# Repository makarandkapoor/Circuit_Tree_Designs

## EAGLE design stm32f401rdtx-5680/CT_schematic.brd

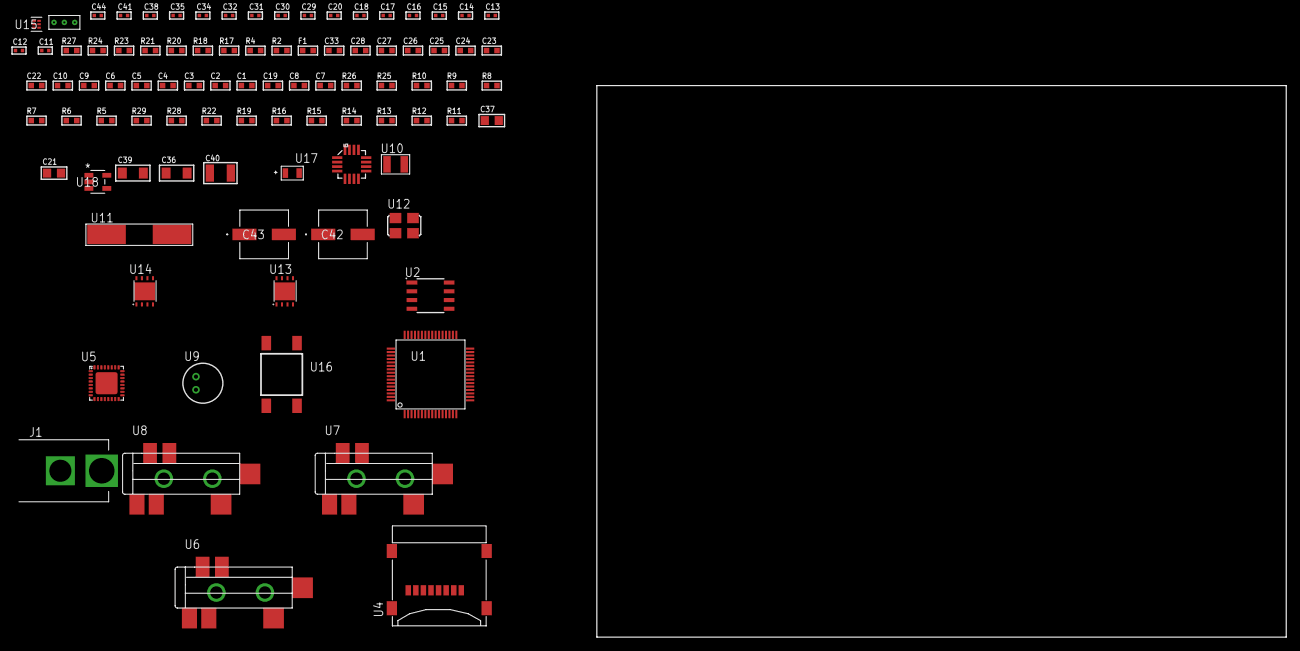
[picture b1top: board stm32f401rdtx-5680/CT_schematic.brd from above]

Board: 2 copper layers, 100.0 x 80.0 mm, 92 parts (0 on the bottom side), 60 nets, no tracks yet.

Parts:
C1, C10, C22, C23, C24, C25, C26, C27, C28, C33: 1e-06; C0603
C2, C3, C4, C5, C6: 1e-07; C0603
C7: 4.7e-06; C0603
C8: 2.2e-06; C0603
C9: 1e-08; C0603
C11, C12, C13, C14: 1e-11; C0402
C15, C16, C17, C18, C34, C35, C38, C44: 1e-08; C0402
C19: 4.7e-07; C0603
C20, C29, C30, C31, C32, C41: 1e-07; C0402
C21, C37: 1e-05; C0805
C36, C39: 1e-05; C1206
C40: 1e-05; C1210
C42, C43: 0.0001; EXV-9H
F1: 240.0; L0603
J1: PJ-037B; PJ-037B_PACKAGE
R2, R21, R24: 1000.0; R0603
R4: 4700.0; R0603
R5, R6, R7, R8, R9, R10, R25, R26: 10000.0; R0603
R11, R12, R13, R14, R15, R16, R19, R22: 100000.0; R0603
R17, R18: 1270.0; R0603
R20: 200.0; R0603
R23: 2231.0; R0603
R27: 9100.0; R0603
R28: 680000.0; R0603
R29: 120000.0; R0603
U1: STM32F401RDT6; LQFP64
U2: AT25320B-SSHL-T; SOIC-8
U3: l3g4200d; LGA-16
U4: 0472192001; MOLEX_47219-2001
U5: SGTL5000XNAA3; QFN-32
U6, U7, U8: SJ-43515TS-SMT-TR
U9: WM-64PCT; WM-64PC
U10: ABS07-32.768KHZ-7-T
U11: ABLS-25.000MHZ-B2F-T
U12: ASFL-24.57MHZ-NCS; ASFL1
U13, U14: LP3878SDX-ADJ/NOPB; WSON-8
U15: TPS3895ADRYR; SON-6
U16: 4-1437565-2; SW_4-1437565-2
U17: Q65110A2395; LGM67K-G1J2-24-Z
U18: nc7sz125m5x; NC7SZ125M5X
U19: Dummy; DUMMY_PACKAGE_195

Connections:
CLK_CRYSTAL_U1_3: C11.1, U1.3, U10.1
CLK_CRYSTAL_U1_4: C12.1, U1.4, U10.2
CLK_CRYSTAL_U1_5: C13.1, U1.5, U11.1
CLK_CRYSTAL_U1_6: C14.1, U1.6, U11.2
CLK_U5_21: U5.21, U12.3
GND: C1.2, C2.2, C3.2, C4.2, C5.2, C6.2, C7.2, C8.2, C9.2, C10.2, C11.2, C12.2, C13.2, C14.2, C15.2, C16.2, C17.2, C18.2, C20.2, C21.2, C29.2, C30.2, C31.2, C32.2, C33.2, C34.2, C35.2, C36.2, C37.2, C38.2, C39.2, C40.2, C41.2, C42.2, C43.2, C44.2, J1.2, R2.2, R5.2, R9.1, R9.2, R18.2, R21.2, R24.2, R27.2, R29.2, U1.12, U1.18, U1.31, U1.47, U1.63, U2.4, U3.8, U3.9, U3.10, U3.11, U3.12, U3.13, U4.6, U4.G1, U4.G2, U4.G3, U4.G4, U5.1, U5.3, U5.7, U5.EXP, U7.1, U8.1, U9.2, U12.2, U13.3, U13.PAD, U14.3, U14.PAD, U15.2, U17.C, U18.1, U18.3, U19.1
NET_U1_7: R4.1, U1.7, U18.4
NET_U1_13: C9.1, C10.1, F1.1, U1.13
NET_U1_30: C8.1, U1.30
NET_U1_60: R5.1, U1.60
NET_U1_61: U16.3, U16.4
NET_U2_3: R6.1, U2.3
NET_U2_7: R8.1, U2.7
NET_U3_14: C18.1, C19.1, U3.14
NET_U5_10: C32.1, U5.10
NET_U5_29: R17.1, U5.29
NET_U5_31: R18.1, U5.31
NET_U6_1: U5.4, U6.1
NET_U6_2: U5.2, U6.2
NET_U6_5: U5.6, U6.5
NET_U7_2: C23.1, U7.2
NET_U7_5: C22.1, U7.5
NET_U8_2: C25.1, C26.1, U8.2
NET_U8_5: C24.1, U8.5
NET_U8_13: C25.2, C26.2
NET_U9_1: C27.1, C28.1, C33.1, U5.16, U9.1
NET_U9_15: C27.2, C28.2
NET_U13_1: C35.1, U13.1
NET_U13_6: R20.2, R21.1, U13.6
NET_U13_8: R19.1, U13.8
NET_U14_1: C38.1, U14.1
NET_U14_6: R23.2, R24.1, U14.6
NET_U14_8: R22.1, U14.8
NET_U15_1: R26.1, R27.1, U15.1
NET_U15_3: R28.2, R29.1, U15.3
NET_U15_4: R25.1, U15.4, U18.2
NET_U16_1: R2.1, U16.1, U16.2
PROC_ADC1_IN1: U1.15, U19.3
PROC_ADC1_IN2: U1.16, U19.2
PROC_I2S2_CK: U1.34, U5.24
PROC_I2S2_EXT_SD: U1.35, U5.25
PROC_I2S2_SD: U1.36, U5.26
PROC_I2S2_WS: U1.62, U5.23
PROC_SDIO_CK: R12.1, U1.53, U4.5
PROC_SDIO_CMD: R11.1, U1.54, U4.3
PROC_SDIO_D0: R13.1, U1.39, U4.7
PROC_SDIO_D1: R14.1, U1.40, U4.8
PROC_SDIO_D2: R15.1, U1.51, U4.1
PROC_SDIO_D3: R16.1, U1.52, U4.2
PROC_SPI1_MISO: U1.22, U3.4
PROC_SPI1_MOSI: U1.23, U3.3
PROC_SPI1_NSS: R10.1, U1.20, U3.5
PROC_SPI1_SCK: U1.21, U3.2
PROC_SPI2_MISO: U1.10, U2.2
PROC_SPI2_MOSI: U1.11, U2.5
PROC_SPI2_NSS: R7.1, U1.33, U2.1
PROC_SPI2_SCK: U1.29, U2.6
VCC_S1_9V6: C36.1, C39.1, C42.1, C43.1, J1.1, R19.2, R22.2, U13.4, U14.4
VCC_TIER1_1V2: C29.1, C37.1, R20.1, U5.30, U13.5
VCC_TIER1_3V3: C1.1, C2.1, C3.1, C4.1, C5.1, C6.1, C7.1, C15.1, C16.1, C17.1, C20.1, C21.1, C30.1, C31.1, C34.1, C40.1, C41.1, C44.1, F1.2, R4.2, R6.2, R7.2, R8.2, R10.2, R11.2, R12.2, R13.2, R14.2, R15.2, R16.2, R17.2, R23.1, R25.2, R26.2, R28.1, U1.1, U1.19, U1.32, U1.48, U1.64, U2.8, U3.1, U3.15, U3.16, U4.4, U5.5, U5.20, U12.4, U14.5, U15.6, U18.5

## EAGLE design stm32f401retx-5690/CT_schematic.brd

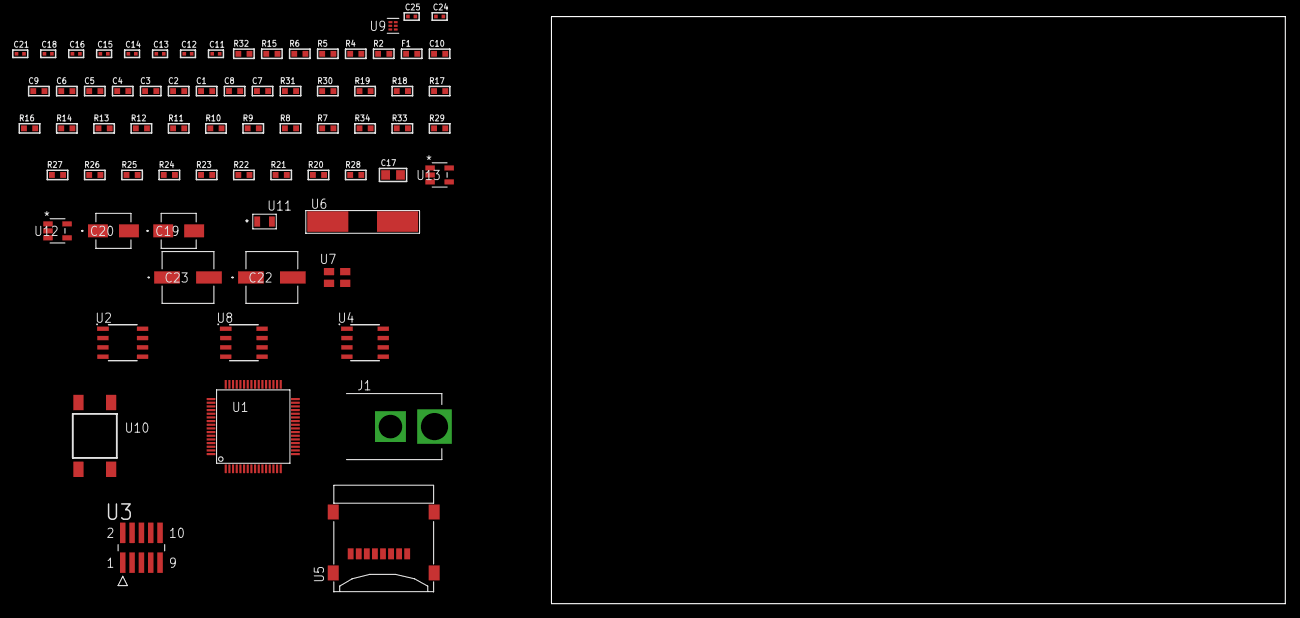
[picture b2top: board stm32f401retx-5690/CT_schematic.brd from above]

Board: 2 copper layers, 100.0 x 80.0 mm, 72 parts (0 on the bottom side), 42 nets, no tracks yet.

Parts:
C1, C10: 1e-06; C0603
C2, C3, C4, C5, C6: 1e-07; C0603
C7: 4.7e-06; C0603
C8: 2.2e-06; C0603
C9: 1e-08; C0603
C11, C12: 1e-11; C0402
C13, C15, C18, C24, C25: 1e-08; C0402
C14, C16, C21: 1e-07; C0402
C17: 1e-05; C0805
C19: 1e-06; EXV-9B
C20: 2.2e-06; EXV-9B
C22, C23: 0.0001; EXV-9H
F1: 240.0; L0603
J1: PJ-037B; PJ-037B_PACKAGE
R2: 1000.0; R0603
R4: 4700.0; R0603
R5, R6: 2200.0; R0603
R7, R8, R9, R10, R11, R12, R13, R14, R16, R17, R18, R19, R30, R31: 10000.0; R0603
R15: 5.0; R0603
R20, R21, R22, R23, R24, R25, R26, R27, R29: 100000.0; R0603
R28: 164658.62; R0603
R32: 9100.0; R0603
R33: 680000.0; R0603
R34: 120000.0; R0603
U1: STM32F401RET6; LQFP64
U2: AT25040B-SSHL-T; SOIC-8
U3: FTSH-105-01-L-DV-K; SAMTEC_FTSH-105-01-L-DV-K
U4: AT24C02D-SSHM-T; AT24C02D
U5: 0472192001; MOLEX_47219-2001
U6: ABLS-25.000MHZ-B2F-T
U7: ASEK-32.768KHz-ECST; ASEK
U8: LP2954AIMX/NOPB; LP2954
U9: TPS3895ADRYR; SON-6
U10: 4-1437565-2; SW_4-1437565-2
U11: Q65110A2395; LGM67K-G1J2-24-Z
U12, U13: nc7sz125m5x; NC7SZ125M5X

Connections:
CLK_CRYSTAL_U1_5: C11.1, U1.5, U6.1
CLK_CRYSTAL_U1_6: C12.1, U1.6, U6.2
CLK_U1_3: U1.3, U7.3
GND: C1.2, C2.2, C3.2, C4.2, C5.2, C6.2, C7.2, C8.2, C9.2, C10.2, C11.2, C12.2, C13.2, C14.2, C15.2, C16.2, C17.2, C18.2, C19.2, C20.2, C21.2, C22.2, C23.2, C24.2, C25.2, J1.2, R2.2, R7.2, R14.2, R15.2, R16.2, R18.2, R19.2, R29.2, R32.2, R34.2, U1.12, U1.18, U1.31, U1.47, U1.63, U2.4, U3.3, U3.5, U4.4, U5.6, U5.G1, U5.G2, U5.G3, U5.G4, U7.2, U8.4, U9.2, U11.C, U12.2, U12.3, U13.1, U13.3
NET_U1_7: R4.1, U1.7, U13.4
NET_U1_13: C9.1, C10.1, F1.1, U1.13
NET_U1_30: C8.1, U1.30
NET_U1_58: R5.1, U1.58, U4.6
NET_U1_59: R6.1, U1.59, U4.5
NET_U1_60: R7.1, U1.60
NET_U1_62: U10.3, U10.4
NET_U2_3: R8.1, U2.3
NET_U2_7: R10.1, U2.7
NET_U3_9: R15.1, U3.9
NET_U4_1: R17.1, U4.1
NET_U4_2: R18.1, U4.2
NET_U4_3: R19.1, U4.3
NET_U4_7: R16.1, U4.7
NET_U8_3: R27.1, U8.3
NET_U8_5: R26.1, U8.5
NET_U8_7: R28.2, R29.1, U8.7
NET_U9_1: R31.1, R32.1, U9.1
NET_U9_3: R33.2, R34.1, U9.3
NET_U9_4: R30.1, U9.4, U12.4, U13.2
NET_U10_1: R2.1, U10.1, U10.2
PROC_SDIO_CK: R21.1, U1.53, U5.5
PROC_SDIO_CMD: R20.1, U1.54, U5.3
PROC_SDIO_D0: R22.1, U1.39, U5.7
PROC_SDIO_D1: R23.1, U1.40, U5.8
PROC_SDIO_D2: R24.1, U1.51, U5.1
PROC_SDIO_D3: R25.1, U1.52, U5.2
PROC_SPI1_MISO: U1.22, U2.2
PROC_SPI1_MOSI: U1.23, U2.5
PROC_SPI1_NSS: R9.1, U1.20, U2.1
PROC_SPI1_SCK: U1.21, U2.6
PROC_SYS_JTCK_SWCLK: R14.1, U1.49, U3.4
PROC_SYS_JTDI: R12.1, U1.50, U3.8
PROC_SYS_JTDO_SWO: U1.55, U3.6
PROC_SYS_JTMS_SWDIO: R13.1, U1.46, U3.2
RST_OUT_U3_JTAG_RST_B: R11.1, U3.10, U12.1
VCC_S1_10V3: C19.1, C22.1, C23.1, J1.1, R27.2, U8.8
VCC_TIER1_3V3: C1.1, C2.1, C3.1, C4.1, C5.1, C6.1, C7.1, C13.1, C14.1, C15.1, C16.1, C17.1, C18.1, C20.1, C21.1, C24.1, C25.1, F1.2, R4.2, R5.2, R6.2, R8.2, R9.2, R10.2, R11.2, R12.2, R13.2, R17.2, R20.2, R21.2, R22.2, R23.2, R24.2, R25.2, R26.2, R28.1, R30.2, R31.2, R33.1, U1.1, U1.19, U1.32, U1.48, U1.64, U2.8, U3.1, U4.8, U5.4, U7.4, U8.1, U9.6, U12.5, U13.5

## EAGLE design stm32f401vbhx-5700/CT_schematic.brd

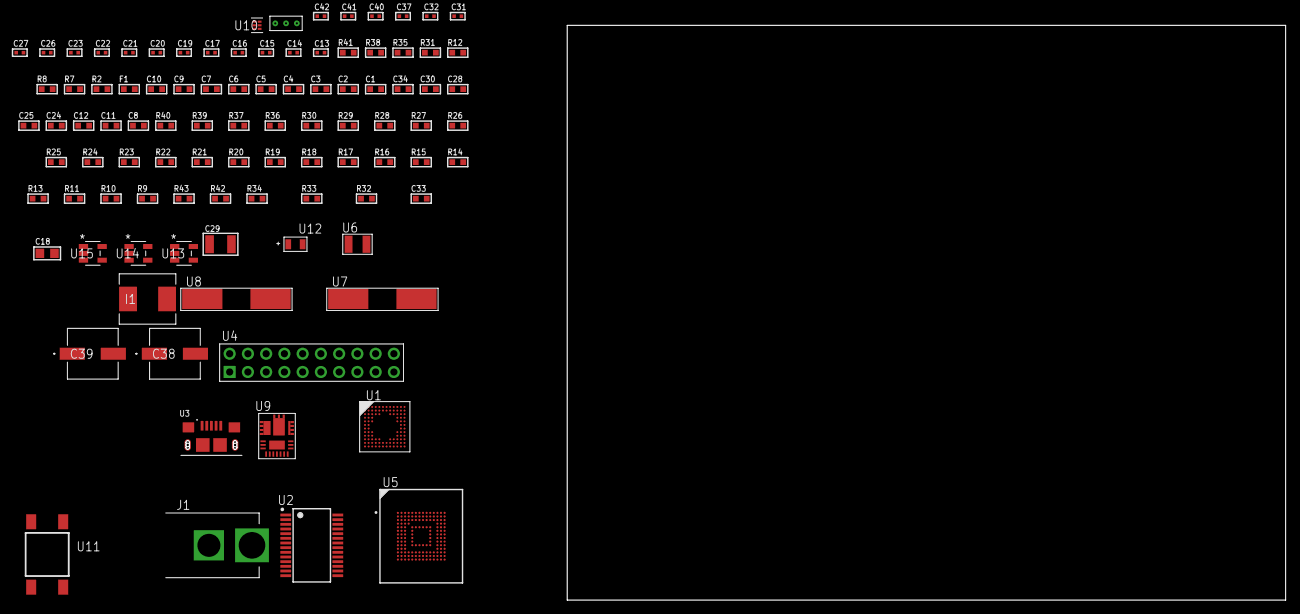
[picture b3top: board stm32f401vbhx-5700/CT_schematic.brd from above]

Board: 2 copper layers, 97 parts (0 on the bottom side), 62 nets, no tracks yet.

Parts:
C1, C10: 1e-06; C0603
C2, C3, C4, C5, C6, C7: 1e-07; C0603
C8: 4.7e-06; C0603
C9: 1e-08; C0603
C11, C12, C24, C25, C28, C30: 2.2e-06; C0603
C13, C14, C15, C16: 1e-11; C0402
C17, C19, C20, C21, C22, C23, C26, C27, C31, C32, C37: 1e-07; C0402
C18: 4.7e-06; C0805
C29: 0.0001; C1210
C33: 7.8444498006919e-09; R0603
C34: 2.7e-07; C0603
C38, C39: 0.0001; EXV-9H
C40, C41, C42: 1e-08; C0402
F1: 240.0; L0603
I1: 6.8e-07; IND25X25CZ
J1: PJ-037B; PJ-037B_PACKAGE
R2: 1000.0; R0603
R7, R8, R12: 4700.0; R0603
R9, R10, R11, R13, R14, R15, R16, R17, R18, R19, R20, R39, R40: 10000.0; R0603
R21, R22, R23, R24, R25, R26, R27, R28, R29, R30: 34000.0; R0603
R31: 0.1; R0603
R32: 4030.2416170974; R0603
R33: 719.68600305311; R0603
R34: 64.984347826087; R0603
R35: 130.0; R0603
R36: 39000.0; R0603
R37: 49900.0; R0603
R38: 5600.0; R0603
R41: 9100.0; R0603
R42: 680000.0; R0603
R43: 120000.0; R0603
U1: STM32F401VBH6; UFBGA100
U2: FT232RL-REEL; SSOP-28
U3: 10118193-0001LF; FCI_10118193-0001LF
U4: TST-110-05-T-D-RA
U5: mtfc4gmcdm; TFBGA-153
U6: ABS07-32.768KHZ-7-T
U7: ABLS-25.000MHZ-B2F-T
U8: ABLS-12.000MHZ-B4-T
U9: IR3899MTR1PBF
U10: TPS3895ADRYR; SON-6
U11: 4-1437565-2; SW_4-1437565-2
U12: Q65110A2395; LGM67K-G1J2-24-Z
U13, U14, U15: nc7sz125m5x; NC7SZ125M5X
U16: Dummy; DUMMY_PACKAGE_207

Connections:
CLK_CRYSTAL_U1_D1: C13.1, U1.D1, U6.1
CLK_CRYSTAL_U1_E1: C14.1, U1.E1, U6.2
CLK_CRYSTAL_U1_F1: C15.1, U1.F1, U7.1
CLK_CRYSTAL_U1_G1: C16.1, U1.G1, U7.2
CLK_CRYSTAL_U2_27: U2.27, U8.1
CLK_CRYSTAL_U2_28: U2.28, U8.2
GND: C1.2, C2.2, C3.2, C4.2, C5.2, C6.2, C7.2, C8.2, C9.2, C10.2, C11.2, C12.2, C13.2, C14.2, C15.2, C16.2, C17.2, C18.2, C19.2, C20.2, C21.2, C22.2, C23.2, C24.2, C25.2, C26.2, C27.2, C28.2, C30.2, C31.2, C32.2, C37.2, C38.2, C39.2, C40.2, C41.2, C42.2, J1.2, R2.2, R9.2, R11.2, R14.2, R20.2, R31.1, R31.2, R33.2, R36.2, R38.2, R41.2, R43.2, U1.D3, U1.F2, U1.F11, U1.F12, U1.J1, U1.K1, U2.7, U2.18, U2.21, U2.25, U2.26, U3.5, U3.6, U3.7, U3.8, U3.9, U4.4, U4.6, U4.8, U4.10, U4.12, U4.14, U4.16, U4.18, U4.20, U5.C4, U5.E7, U5.G5, U5.H10, U5.K8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
NET_U1_A4: R9.1, U1.A4
NET_U1_C11: C12.1, U1.C11
NET_U1_E3: R11.1, U1.E3
NET_U1_H2: R8.1, U1.H2, U15.4
NET_U1_H3: R10.1, U1.H3
NET_U1_L11: C11.1, U1.L11
NET_U1_M1: C9.1, C10.1, F1.1, U1.L1, U1.M1
NET_U1_M12: U11.3, U11.4
NET_U2_14: R13.1, U2.14
NET_U2_17: C19.1, U2.17
NET_U2_19: R14.1, U2.19
NET_U3_1: R12.1, U3.1
NET_U3_2: U2.16, U3.2
NET_U3_3: U2.15, U3.3
NET_U4_19: R20.1, U4.19
NET_U5_C2: C25.1, C26.1, U5.C2
NET_U5_K5: R7.1, U5.K5, U14.4
NET_U9_1: C33.1, R32.1, R33.1, R34.1, R35.1, U9.1, U9.8
NET_U9_2: C32.1, U9.2
NET_U9_3: C33.2, C34.1, C34.2, U9.3
NET_U9_5: R36.1, U9.5
NET_U9_10: C30.1, U9.10
NET_U9_12: C29.1, I1.1, U9.12
NET_U9_14: C29.2, U9.14
NET_U9_15: R37.1, R38.1, U9.15
NET_U9_ATNET_3: I1.2, R32.2
NET_U9_ATNET_4: C34.2, R34.2
NET_U10_1: R40.1, R41.1, U10.1
NET_U10_3: R42.2, R43.1, U10.3
NET_U10_4: R39.1, U10.4, U13.4, U14.2, U15.2
NET_U11_1: R2.1, U11.1, U11.2
PROC_ADC1_IN1: U1.M2, U16.3
PROC_ADC1_IN2: U1.K3, U16.2
PROC_SDIO_CK: R30.1, U1.B10, U5.M6
PROC_SDIO_CMD: R29.1, U1.C8, U5.M5
PROC_SDIO_D0: R21.1, U1.E10, U5.A3
PROC_SDIO_D1: R22.1, U1.D12, U5.A4
PROC_SDIO_D2: R23.1, U1.B11, U5.A5
PROC_SDIO_D3: R24.1, U1.C10, U5.B2
PROC_SDIO_D4: R25.1, U1.A3, U5.B3
PROC_SDIO_D5: R26.1, U1.B3, U5.B4
PROC_SDIO_D6: R27.1, U1.E12, U5.B5
PROC_SDIO_D7: R28.1, U1.E11, U5.B6
PROC_SYS_JTCK_SWCLK: R18.1, U1.A10, U4.9
PROC_SYS_JTDI: R16.1, U1.A9, U4.5
PROC_SYS_JTDO_SWO: U1.A8, U4.13
PROC_SYS_JTMS_SWDIO: R17.1, U1.A11, U4.7
PROC_SYS_JTRST: R15.1, U1.A7, U4.3
PROC_USART1_CTS: U1.B12, U2.3
PROC_USART1_RTS: U1.A12, U2.11
PROC_USART1_RX: U1.B4, U2.1
PROC_USART1_TX: U1.B5, U2.5
RST_OUT_U4_SRESET_B: R19.1, U4.15, U13.1
VCC_S1_16V1: C31.1, C38.1, C39.1, J1.1, R37.2, U9.9
VCC_TIER1_3V3: C1.1, C2.1, C3.1, C4.1, C5.1, C6.1, C7.1, C8.1, C17.1, C18.1, C20.1, C21.1, C22.1, C23.1, C24.1, C27.1, C28.1, C37.1, C40.1, C41.1, C42.1, F1.2, I1.2, R7.2, R8.2, R10.2, R13.2, R15.2, R16.2, R17.2, R18.2, R19.2, R21.2, R22.2, R23.2, R24.2, R25.2, R26.2, R27.2, R28.2, R29.2, R30.2, R32.2, R39.2, R40.2, R42.1, U1.C4, U1.E2, U1.G2, U1.G11, U1.G12, U2.4, U2.20, U4.1, U4.2, U5.C6, U5.E6, U5.F5, U5.J10, U5.K9, U5.M4, U5.N4, U5.P3, U5.P5, U10.6, U13.5, U14.5, U15.5

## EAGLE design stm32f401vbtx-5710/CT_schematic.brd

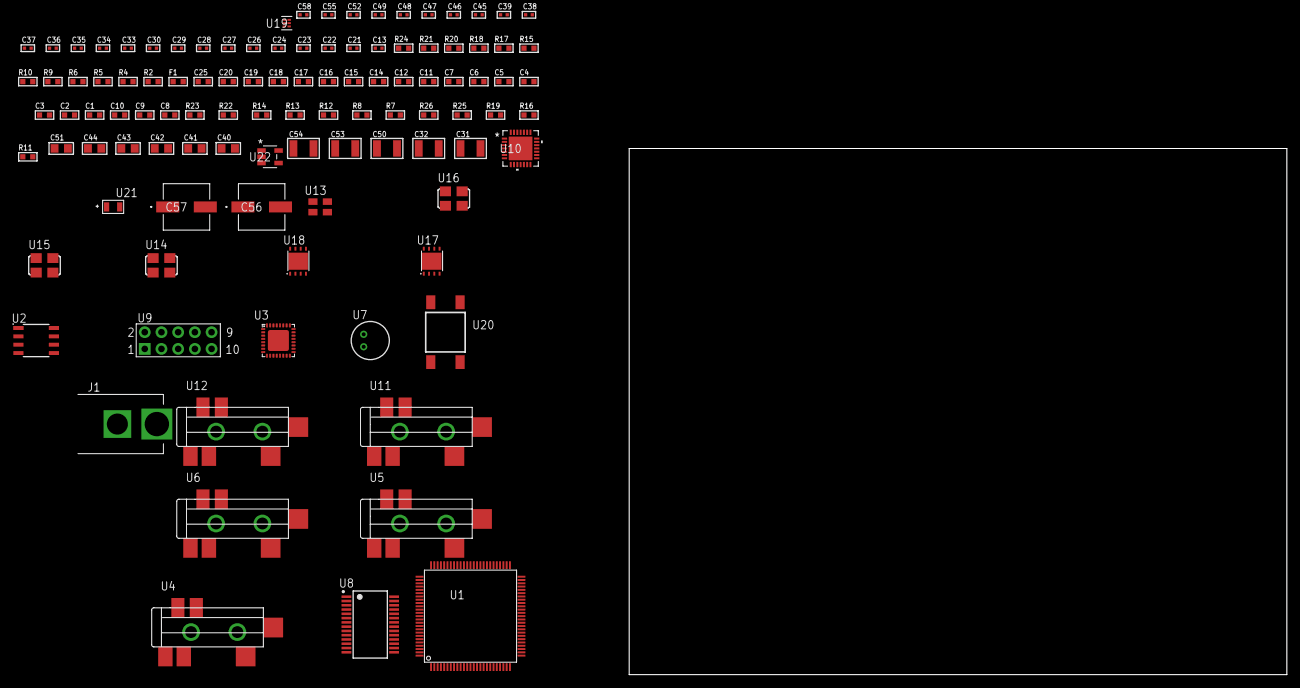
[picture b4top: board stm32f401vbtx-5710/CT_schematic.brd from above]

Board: 2 copper layers, 100.0 x 80.0 mm, 106 parts (0 on the bottom side), 67 nets, no tracks yet.

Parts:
C1, C12, C14, C15, C16, C17, C18, C19, C20, C25: 1e-06; C0603
C2, C3, C4, C5, C6, C7: 1e-07; C0603
C8: 4.7e-06; C0603
C9, C10: 2.2e-06; C0603
C11: 1e-08; C0603
C13, C45, C46, C47, C48, C49, C52, C58: 1e-08; C0402
C21, C22, C23, C24, C26, C27, C28, C29, C30, C35, C36, C37, C38, C39, C55: 1e-07; C0402
C31, C32: 2.2e-05; C1210
C33, C34: 1e-09; C0402
C40, C41, C42, C43, C44, C51: 1e-05; C0805
C50, C53, C54: 1e-05; C1210
C56, C57: 0.0001; EXV-9H
F1: 240.0; L0603
J1: PJ-037B; PJ-037B_PACKAGE
R2, R18, R21: 1000.0; R0603
R4: 4700.0; R0603
R5, R6: 2200.0; R0603
R7, R8, R22, R23: 10000.0; R0603
R9, R10: 1270.0; R0603
R11, R16, R19: 100000.0; R0603
R12, R13, R14: 47000.0; R0603
R15: 680.0; R0603
R17: 200.0; R0603
R20: 2231.0; R0603
R24: 9100.0; R0603
R25: 680000.0; R0603
R26: 120000.0; R0603
U1: STM32F401VBT6; LQFP100
U2: M24M02-DRMN6TP; SOIC-8
U3: SGTL5000XNAA3; QFN-32
U4, U5, U6, U11, U12: SJ-43515TS-SMT-TR
U7: WM-64PCT; WM-64PC
U8: ST3241EBPR; SSOP-28
U9: HTSS-105-01-G-D
U10: WM8731CLSEFL; QFN-28
U13: ASEK-32.768KHz-ECST; ASEK
U14: ASFL1-12.288MHZ-EC-T; ASFL1
U15: ASFL-24.57MHZ-NCS; ASFL1
U16: ASFL1-25MHZ-NCS; ASFL1
U17, U18: LP3878SDX-ADJ/NOPB; WSON-8
U19: TPS3895ADRYR; SON-6
U20: 4-1437565-2; SW_4-1437565-2
U21: Q65110A2395; LGM67K-G1J2-24-Z
U22: nc7sz125m5x; NC7SZ125M5X

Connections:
CLK_U1_8: U1.8, U13.3
CLK_U1_12: U1.12, U16.3
CLK_U3_21: U3.21, U15.3
CLK_U10_1: U10.1, U14.3
GND: C1.2, C2.2, C3.2, C4.2, C5.2, C6.2, C7.2, C8.2, C9.2, C10.2, C11.2, C12.2, C13.2, C21.2, C22.2, C23.2, C24.2, C25.2, C26.2, C29.2, C30.2, C34.2, C35.2, C36.2, C37.2, C38.2, C39.2, C40.2, C41.2, C42.2, C43.2, C44.2, C45.2, C46.2, C47.2, C48.2, C49.2, C50.2, C51.2, C52.2, C53.2, C54.2, C55.2, C56.2, C57.2, C58.2, J1.2, R2.2, R7.2, R8.2, R10.2, R12.2, R13.2, R14.2, R18.2, R21.2, R24.2, R26.2, U1.10, U1.20, U1.27, U1.49, U1.74, U1.99, U2.4, U3.1, U3.3, U3.7, U3.EXP, U5.1, U6.1, U7.2, U8.23, U8.25, U9.9, U10.4, U10.15, U10.19, U10.25, U10.26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
NET_U1_14: R4.1, U1.14, U22.4
NET_U1_22: C11.1, C12.1, F1.1, U1.21, U1.22
NET_U1_48: C9.1, U1.48
NET_U1_73: C10.1, U1.73
NET_U1_92: R5.1, U1.92, U2.6
NET_U1_93: R6.1, U1.93, U2.5
NET_U1_94: R7.1, U1.94
NET_U1_98: U20.3, U20.4
NET_U2_3: R8.1, U2.3
NET_U3_10: C24.1, U3.10
NET_U3_29: R9.1, U3.29
NET_U3_31: R10.1, U3.31
NET_U4_1: U3.4, U4.1
NET_U4_2: U3.2, U4.2
NET_U4_5: U3.6, U4.5
NET_U5_2: C15.1, U5.2
NET_U5_5: C14.1, U5.5
NET_U6_2: C17.1, C18.1, U6.2
NET_U6_5: C16.1, U6.5
NET_U6_13: C17.2, C18.2
NET_U7_1: C19.1, C20.1, C25.1, U3.16, U7.1
NET_U7_15: C19.2, C20.2
NET_U8_1: C28.1, U8.1
NET_U8_2: C28.2, U8.2
NET_U8_3: C30.1, U8.3
NET_U8_22: R11.1, U8.22
NET_U8_24: C27.2, U8.24
NET_U8_27: C29.1, U8.27
NET_U8_28: C27.1, U8.28
NET_U9_3: U8.4, U9.3
NET_U9_4: U8.5, U9.4
NET_U9_5: U8.9, U9.5
NET_U9_6: U8.10, U9.6
NET_U10_20: C39.1, C44.1, U10.20
NET_U11_2: C32.1, R13.1, U11.2
NET_U11_5: C31.1, R12.1, U11.5
NET_U12_5: C33.1, C34.1, R14.1, R15.1, U12.5
NET_U17_1: C49.1, U17.1
NET_U17_6: R17.2, R18.1, U17.6
NET_U17_8: R16.1, U17.8
NET_U18_1: C52.1, U18.1
NET_U18_6: R20.2, R21.1, U18.6
NET_U18_8: R19.1, U18.8
NET_U19_1: R23.1, R24.1, U19.1
NET_U19_3: R25.2, R26.1, U19.3
NET_U19_4: R22.1, U19.4, U22.2
NET_U20_1: R2.1, U20.1, U20.2
PROC_I2S2_CK: U1.47, U10.7
PROC_I2S2_EXT_SD: U1.17, U10.10
PROC_I2S2_SD: U1.18, U10.8
PROC_I2S2_WS: U1.51, U10.9, U10.11
PROC_I2S3_CK: U1.78, U3.24
PROC_I2S3_EXT_SD: U1.79, U3.25
PROC_I2S3_SD: U1.80, U3.26
PROC_I2S3_WS: U1.29, U3.23
PROC_USART1_CTS: U1.70, U8.13
PROC_USART1_RTS: U1.71, U8.18
PROC_USART1_RX: U1.69, U8.19
PROC_USART1_TX: U1.68, U8.14
VCC_S1_13V6: C50.1, C53.1, C56.1, C57.1, J1.1, R16.2, R19.2, U17.4, U18.4
VCC_TIER1_1V2: C21.1, C51.1, R17.1, U3.30, U17.5
VCC_TIER1_3V3: C1.1, C2.1, C3.1, C4.1, C5.1, C6.1, C7.1, C8.1, C13.1, C22.1, C23.1, C26.1, C35.1, C36.1, C37.1, C38.1, C40.1, C41.1, C42.1, C43.1, C45.1, C46.1, C47.1, C48.1, C54.1, C55.1, C58.1, F1.2, R4.2, R5.2, R6.2, R9.2, R11.2, R20.1, R22.2, R23.2, R25.1, U1.6, U1.11, U1.19, U1.28, U1.50, U1.75, U1.100, U2.8, U3.5, U3.20, U8.26, U10.3, U10.5, U10.12, U10.18, U13.4, U14.4, U15.4, U16.4, U18.5, U19.6, U22.5

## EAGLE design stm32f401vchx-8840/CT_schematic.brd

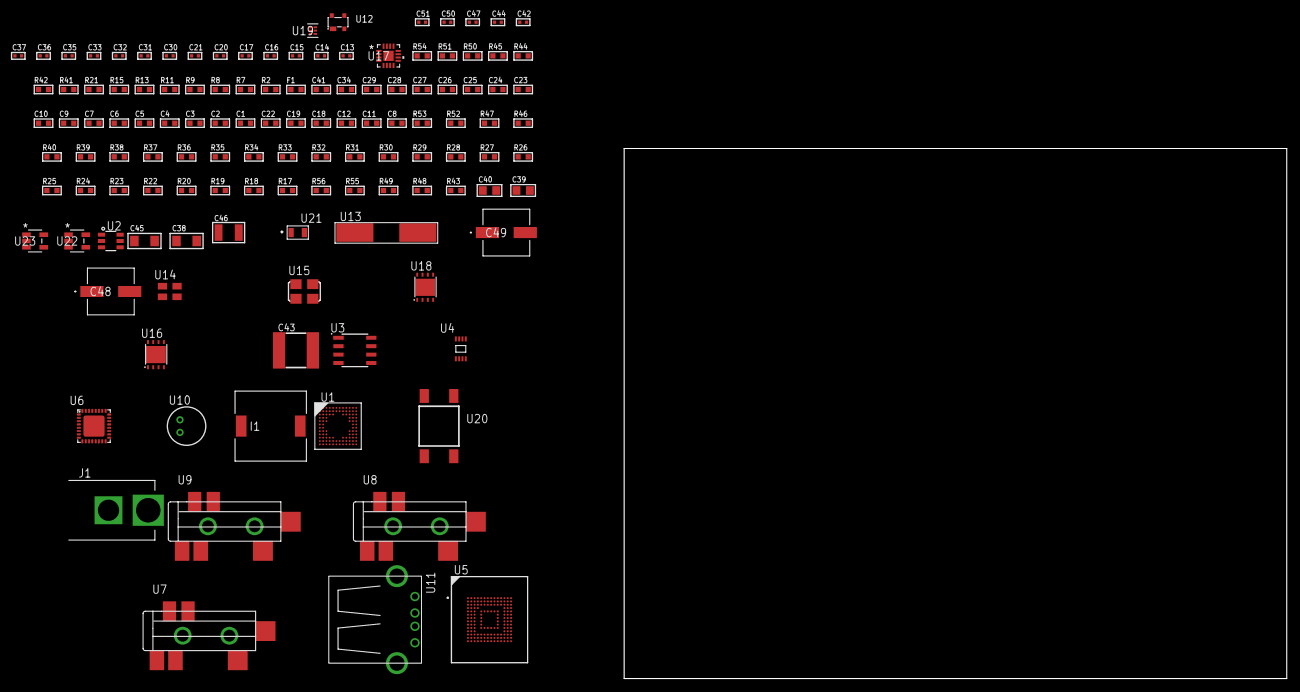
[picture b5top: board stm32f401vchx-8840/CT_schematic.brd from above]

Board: 2 copper layers, 100.0 x 80.0 mm, 124 parts (0 on the bottom side), 80 nets, no tracks yet.

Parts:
C1, C10, C23, C24, C25, C26, C27, C28, C29, C34, C41: 1e-06; C0603
C2, C3, C4, C5, C6, C7: 1e-07; C0603
C8: 4.7e-06; C0603
C9: 1e-08; C0603
C11, C12, C18, C19, C22: 2.2e-06; C0603
C13, C14: 1e-11; C0402
C15, C16, C35, C36, C37, C44, C50, C51: 1e-08; C0402
C17, C20, C21, C30, C31, C32, C33, C42, C47: 1e-07; C0402
C38, C45: 1e-05; C1206
C39, C40: 1e-05; C0805
C43: 6.8e-05; 2220
C46: 1e-05; C1210
C48, C49: 0.0001; EXV-9H
F1: 240.0; L0603
I1: 3.8e-06; DR1040
J1: PJ-037B; PJ-037B_PACKAGE
R2, R45, R51: 1000.0; R0603
R7, R8: 4700.0; R0603
R9, R11, R13, R15: 2200.0; R0603
R17: 47000.0; R0603
R18, R19, R20, R22, R23, R24, R25, R26, R27, R28, R29, R30, R52, R53: 10000.0; R0603
R21, R41, R42: 1270.0; R0603
R31, R32, R33, R34, R35, R36, R37, R38, R39, R40: 34000.0; R0603
R43, R49: 100000.0; R0603
R44: 200.0; R0603
R46: 20000.0; R0603
R47: 91000.0; R0603
R48: 300000.0; R0603
R50: 3900.0; R0603
R54: 9100.0; R0603
R55: 680000.0; R0603
R56: 120000.0; R0603
U1: stm32f401VCH7; UFBGA100
U2: MAX4995AAUT+T; SOT-23-6
U3: AT24C02D-SSHM-T; AT24C02D
U4: 24AA32AT-I/MNY; TDFN-8/6MM
U5: mtfc4gmcdm; TFBGA-153
U6: SGTL5000XNAA3; QFN-32
U7, U8, U9: SJ-43515TS-SMT-TR
U10: WM-64PCT; WM-64PC
U11: 61400416021; USB-A-H
U12: prtr5v0u2ax; SOT143B
U13: ABLS-25.000MHZ-B2F-T
U14: ASEK-32.768KHz-ECST; ASEK
U15: ASFL-24.57MHZ-NCS; ASFL1
U16, U18: LP3878SDX-ADJ/NOPB; WSON-8
U17: LTC3601EUD#PBF; QFN-16_EP
U19: TPS3895ADRYR; SON-6
U20: 4-1437565-2; SW_4-1437565-2
U21: Q65110A2395; LGM67K-G1J2-24-Z
U22, U23: nc7sz125m5x; NC7SZ125M5X

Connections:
CLK_CRYSTAL_U1_F1: C13.1, U1.F1, U13.1
CLK_CRYSTAL_U1_G1: C14.1, U1.G1, U13.2
CLK_U1_D1: U1.D1, U14.3
CLK_U6_21: U6.21, U15.3
GND: C1.2, C2.2, C3.2, C4.2, C5.2, C6.2, C7.2, C8.2, C9.2, C10.2, C11.2, C12.2, C13.2, C14.2, C15.2, C16.2, C17.2, C18.2, C19.2, C20.2, C21.2, C22.2, C30.2, C31.2, C32.2, C33.2, C34.2, C35.2, C36.2, C37.2, C38.2, C39.2, C40.2, C41.2, C43.1, C43.2, C44.2, C45.2, C46.2, C47.2, C48.2, C49.2, C50.2, C51.2, J1.2, R2.2, R17.2, R18.2, R20.2, R21.2, R23.2, R24.2, R26.2, R27.2, R28.2, R30.2, R42.2, R45.2, R46.2, R48.2, R51.2, R54.2, R56.2, U1.D3, U1.F2, U1.F11, U1.F12, U1.J1, U1.K1, U2.2, U3.4, U4.4, U5.C4, U5.E7, U5.G5, U5.H10, U5.K8, U5.N2, U5.N5, U5.P4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
NET_U1_A4: R18.1, U1.A4
NET_U1_A8: R15.1, U1.A8, U4.5
NET_U1_B4: R11.1, U1.B4, U3.5
NET_U1_B5: R9.1, U1.B5, U3.6
NET_U1_C11: C12.1, U1.C11
NET_U1_C12: R21.1, U1.C12
NET_U1_E3: R20.1, U1.E3
NET_U1_H2: R8.1, U1.H2, U23.4
NET_U1_H3: R19.1, U1.H3
NET_U1_L10: R13.1, U1.L10, U4.6
NET_U1_L11: C11.1, U1.L11
NET_U1_M1: C9.1, C10.1, F1.1, U1.L1, U1.M1
NET_U1_M12: U20.3, U20.4
NET_U2_3: R17.1, U2.3
NET_U3_1: R25.1, U3.1
NET_U3_2: R26.1, U3.2
NET_U3_3: R27.1, U3.3
NET_U3_7: R24.1, U3.7
NET_U4_1: R28.1, U4.1
NET_U4_2: R29.1, U4.2
NET_U4_3: R30.1, U4.3
NET_U5_C2: C19.1, C20.1, U5.C2
NET_U5_K5: R7.1, U5.K5, U22.4
NET_U6_10: C33.1, U6.10
NET_U6_29: R41.1, U6.29
NET_U6_31: R42.1, U6.31
NET_U7_1: U6.4, U7.1
NET_U7_2: U6.2, U7.2
NET_U7_5: U6.6, U7.5
NET_U8_2: C24.1, U8.2
NET_U8_5: C23.1, U8.5
NET_U9_2: C26.1, C27.1, U9.2
NET_U9_5: C25.1, U9.5
NET_U9_13: C26.2, C27.2
NET_U10_1: C28.1, C29.1, C34.1, U6.16, U10.1
NET_U10_15: C28.2, C29.2
NET_U16_1: C37.1, U16.1
NET_U16_6: R44.2, R45.1, U16.6
NET_U16_8: R43.1, U16.8
NET_U17_3: C42.2, I1.1, U17.3, U17.4
NET_U17_6: C42.1, U17.6
NET_U17_7: C41.1, U17.7, U17.12
NET_U17_10: R48.1, U17.10
NET_U17_11: R46.1, R47.1, U17.11
NET_U17_ATNET_3: I1.2, R47.2
NET_U18_1: C44.1, U18.1
NET_U18_6: R50.2, R51.1, U18.6
NET_U18_8: R49.1, U18.8
NET_U19_1: R53.1, R54.1, U19.1
NET_U19_3: R55.2, R56.1, U19.3
NET_U19_4: R52.1, U19.4, U22.2, U23.2
NET_U20_1: R2.1, U20.1, U20.2
PROC_GPIO_TO_U1_USB_FAULT: R22.1, U1.A2, U2.6
PROC_GPIO_TO_U1_VBUS_EN: R23.1, U1.A1, U2.4
PROC_I2S2_CK: U1.B8, U6.24
PROC_I2S2_EXT_SD: U1.J3, U6.25
PROC_I2S2_SD: U1.K2, U6.26
PROC_I2S2_WS: U1.L12, U6.23
PROC_SDIO_CK: R40.1, U1.B10, U5.M6
PROC_SDIO_CMD: R39.1, U1.C8, U5.M5
PROC_SDIO_D0: R31.1, U1.E10, U5.A3
PROC_SDIO_D1: R32.1, U1.D12, U5.A4
PROC_SDIO_D2: R33.1, U1.B11, U5.A5
PROC_SDIO_D3: R34.1, U1.C10, U5.B2
PROC_SDIO_D4: R35.1, U1.A3, U5.B3
PROC_SDIO_D5: R36.1, U1.B3, U5.B4
PROC_SDIO_D6: R37.1, U1.E12, U5.B5
PROC_SDIO_D7: R38.1, U1.E11, U5.B6
PROC_USB_OTG_FS_DM: U1.B12, U11.2, U12.3
PROC_USB_OTG_FS_DP: U1.A12, U11.3, U12.2
PROC_USB_OTG_FS_VBUS: U1.D10, U2.1, U11.1, U12.4
VCC_S1_7V8: C38.1, C40.1, C45.1, C48.1, C49.1, J1.1, R43.2, R49.2, U16.4, U17.15, U17.16, U18.4
VCC_TIER1_1V2: C30.1, C39.1, R44.1, U6.30, U16.5
VCC_TIER1_3V3: C1.1, C2.1, C3.1, C4.1, C5.1, C6.1, C7.1, C8.1, C15.1, C16.1, C17.1, C18.1, C21.1, C22.1, C31.1, C32.1, C35.1, C36.1, C43.2, C47.1, C50.1, C51.1, F1.2, I1.2, R7.2, R8.2, R9.2, R11.2, R13.2, R15.2, R19.2, R22.2, R25.2, R29.2, R31.2, R32.2, R33.2, R34.2, R35.2, R36.2, R37.2, R38.2, R39.2, R40.2, R41.2, R47.2, R52.2, R53.2, R55.1, U1.C4, U1.E2, U1.G2, U1.G11, U1.G12, U3.8, U4.7, U4.8, U5.C6, U5.E6, U5.F5, U5.J10, U5.K9, U5.M4, U5.N4, U5.P3, U5.P5, U6.5, U6.20, U14.4, U15.4, U17.8, U19.6, U22.5, U23.5
VCC_TIER1_5V0: C46.1, R50.1, U2.5, U18.5

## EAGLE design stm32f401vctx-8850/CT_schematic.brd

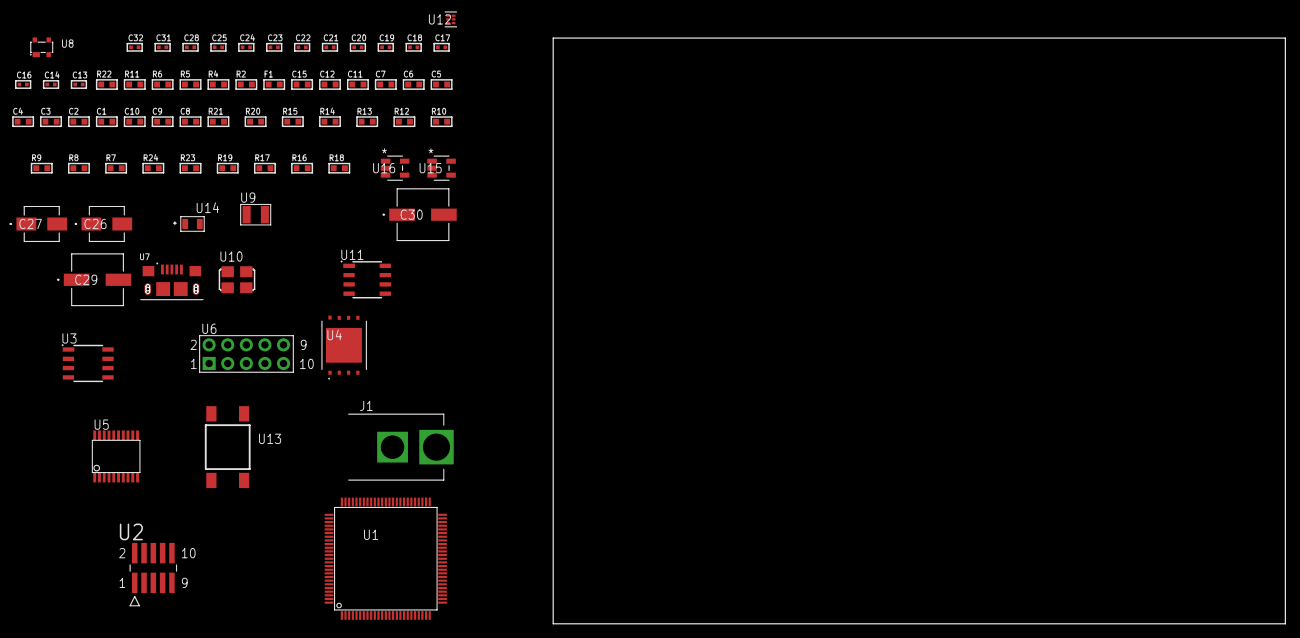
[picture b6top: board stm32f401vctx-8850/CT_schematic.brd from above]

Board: 2 copper layers, 72 parts (0 on the bottom side), 50 nets, no tracks yet.

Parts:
C1, C12, C15: 1e-06; C0603
C2, C3, C4, C5, C6, C7: 1e-07; C0603
C8: 4.7e-06; C0603
C9, C10: 2.2e-06; C0603
C11: 1e-08; C0603
C13, C14: 1e-11; C0402
C16, C19, C20, C21, C22, C23, C24, C28: 1e-07; C0402
C17, C18, C25, C31, C32: 1e-08; C0402
C26: 1e-06; EXV-9B
C27: 2.2e-06; EXV-9B
C29, C30: 0.0001; EXV-9H
F1: 240.0; L0603
J1: PJ-037B; PJ-037B_PACKAGE
R2: 1000.0; R0603
R4: 4700.0; R0603
R5, R6: 2200.0; R0603
R7, R8, R9, R10, R12, R13, R14, R15, R20, R21: 10000.0; R0603
R11: 5.0; R0603
R16, R17, R19: 100000.0; R0603
R18: 164658.62; R0603
R22: 9100.0; R0603
R23: 680000.0; R0603
R24: 120000.0; R0603
U1: stm32f401VCT6; LQFP100
U2: FTSH-105-01-L-DV-K; SAMTEC_FTSH-105-01-L-DV-K
U3: M24M02-DRMN6TP; SOIC-8
U4: S25FL128SDPNFI001; WNG008
U5: SP3203ECY-L/TR; TSSOP20-I
U6: HTSS-105-01-G-D
U7: 10118193-0001LF; FCI_10118193-0001LF
U8: prtr5v0u2ax; SOT143B
U9: ABS07-32.768KHZ-7-T
U10: ASFL1-25MHZ-NCS; ASFL1
U11: LP2954AIMX/NOPB; LP2954
U12: TPS3895ADRYR; SON-6
U13: 4-1437565-2; SW_4-1437565-2
U14: Q65110A2395; LGM67K-G1J2-24-Z
U15, U16: nc7sz125m5x; NC7SZ125M5X

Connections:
CLK_CRYSTAL_U1_8: C13.1, U1.8, U9.1
CLK_CRYSTAL_U1_9: C14.1, U1.9, U9.2
CLK_U1_12: U1.12, U10.3
GND: C1.2, C2.2, C3.2, C4.2, C5.2, C6.2, C7.2, C8.2, C9.2, C10.2, C11.2, C12.2, C13.2, C14.2, C15.2, C16.2, C17.2, C18.2, C19.2, C20.2, C23.2, C24.2, C25.2, C26.2, C27.2, C28.2, C29.2, C30.2, C31.2, C32.2, J1.2, R2.2, R7.2, R11.2, R12.2, R19.2, R22.2, R24.2, U1.10, U1.20, U1.27, U1.49, U1.70, U1.74, U1.99, U2.3, U2.5, U3.4, U4.4, U4.PAD, U5.18, U6.9, U7.5, U7.6, U7.7, U7.8, U7.9, U8.1, U10.2, U11.4, U12.2, U14.C, U15.2, U15.3, U16.1, U16.3
NET_U1_14: R4.1, U1.14, U16.4
NET_U1_22: C11.1, C12.1, F1.1, U1.21, U1.22
NET_U1_48: C9.1, U1.48
NET_U1_73: C10.1, U1.73
NET_U1_92: R5.1, U1.92, U3.6
NET_U1_93: R6.1, U1.93, U3.5
NET_U1_94: R7.1, U1.94
NET_U1_98: U13.3, U13.4
NET_U2_9: R11.1, U2.9
NET_U3_3: R12.1, U3.3
NET_U4_3: R13.1, U4.3
NET_U4_7: R15.1, U4.7
NET_U5_1: C21.1, U5.1
NET_U5_2: C23.1, U5.2
NET_U5_3: C21.2, U5.3
NET_U5_4: C22.1, U5.4
NET_U5_5: C22.2, U5.5
NET_U5_6: C24.1, U5.6
NET_U6_3: U5.14, U6.3
NET_U6_4: U5.13, U6.4
NET_U6_5: U5.17, U6.5
NET_U6_6: U5.16, U6.6
NET_U11_3: R17.1, U11.3
NET_U11_5: R16.1, U11.5
NET_U11_7: R18.2, R19.1, U11.7
NET_U12_1: R21.1, R22.1, U12.1
NET_U12_3: R23.2, R24.1, U12.3
NET_U12_4: R20.1, U12.4, U15.4, U16.2
NET_U13_1: R2.1, U13.1, U13.2
PROC_SPI1_MISO: U1.31, U4.2
PROC_SPI1_MOSI: U1.32, U4.5
PROC_SPI1_NSS: R14.1, U1.29, U4.1
PROC_SPI1_SCK: U1.30, U4.6
PROC_SYS_JTCK_SWCLK: R9.1, U1.76, U2.4
PROC_SYS_JTDO_SWO: U1.89, U2.6
PROC_SYS_JTMS_SWDIO: R10.1, U1.72, U2.2
PROC_USART2_CTS: U1.23, U5.8
PROC_USART2_RTS: U1.24, U5.10
PROC_USART2_RX: U1.26, U5.11
PROC_USART2_TX: U1.25, U5.7
PROC_USB_OTG_FS_DM: U1.70, U7.2, U8.3
PROC_USB_OTG_FS_DP: U1.71, U7.3, U8.2
PROC_USB_OTG_FS_VBUS: C15.1, U1.68, U7.1, U8.4
RST_OUT_U2_JTAG_RST_B: R8.1, U2.10, U15.1
VCC_S1_9V5: C26.1, C29.1, C30.1, J1.1, R17.2, U11.8
VCC_TIER1_3V3: C1.1, C2.1, C3.1, C4.1, C5.1, C6.1, C7.1, C8.1, C16.1, C17.1, C18.1, C19.1, C20.1, C25.1, C27.1, C28.1, C31.1, C32.1, F1.2, R4.2, R5.2, R6.2, R8.2, R9.2, R10.2, R13.2, R14.2, R15.2, R16.2, R18.1, R20.2, R21.2, R23.1, U1.6, U1.11, U1.19, U1.28, U1.50, U1.75, U1.100, U2.1, U3.8, U4.8, U5.12, U5.19, U10.4, U11.1, U12.6, U15.5, U16.5

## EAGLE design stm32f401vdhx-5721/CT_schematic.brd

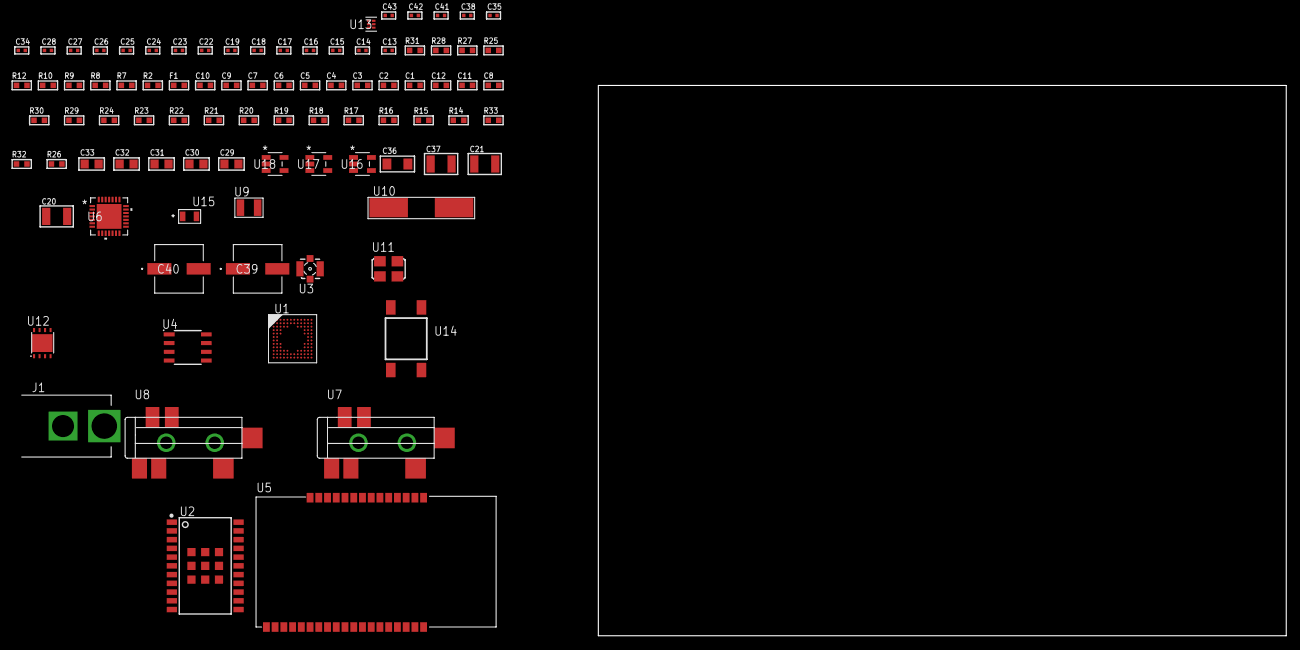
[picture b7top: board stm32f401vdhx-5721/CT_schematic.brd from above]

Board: 2 copper layers, 100.0 x 80.0 mm, 89 parts (0 on the bottom side), 50 nets, no tracks yet.

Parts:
C1, C10: 1e-06; C0603
C2, C3, C4, C5, C6, C7: 1e-07; C0603
C8: 4.7e-06; C0603
C9: 1e-08; C0603
C11, C12: 2.2e-06; C0603
C13, C14, C15, C16: 1e-11; C0402
C17, C19, C24, C25, C26, C27, C28, C38: 1e-07; C0402
C18, C34, C35, C41, C42, C43: 1e-08; C0402
C20, C21: 2.2e-05; C1210
C22, C23: 1e-09; C0402
C29, C30, C31, C32, C33: 1e-05; C0805
C36: 1e-05; C1206
C37: 1e-05; C1210
C39, C40: 0.0001; EXV-9H
F1: 240.0; L0603
J1: PJ-037B; PJ-037B_PACKAGE
R2, R28: 1000.0; R0603
R7, R8, R9: 4700.0; R0603
R10, R12: 2200.0; R0603
R14, R15, R16, R17, R18, R19, R20, R21, R29, R30: 10000.0; R0603
R22, R23, R24: 47000.0; R0603
R25: 680.0; R0603
R26: 100000.0; R0603
R27: 2231.0; R0603
R31: 9100.0; R0603
R32: 680000.0; R0603
R33: 120000.0; R0603
U1: STM32F401VDH6; UFBGA100
U2: A2200-A
U3: 73412-0114; COAXIAL_C
U4: AT25020B-SSHL-T; SOIC-8
U5: ETRX3587
U6: WM8731CLSEFL; QFN-28
U7, U8: SJ-43515TS-SMT-TR
U9: ABS07-32.768KHZ-7-T
U10: ABLS-25.000MHZ-B2F-T
U11: ASFL1-12.288MHZ-EC-T; ASFL1
U12: LP3878SDX-ADJ/NOPB; WSON-8
U13: TPS3895ADRYR; SON-6
U14: 4-1437565-2; SW_4-1437565-2
U15: Q65110A2395; LGM67K-G1J2-24-Z
U16, U17, U18: nc7sz125m5x; NC7SZ125M5X

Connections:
CLK_CRYSTAL_U1_D1: C13.1, U1.D1, U9.1
CLK_CRYSTAL_U1_E1: C14.1, U1.E1, U9.2
CLK_CRYSTAL_U1_F1: C15.1, U1.F1, U10.1
CLK_CRYSTAL_U1_G1: C16.1, U1.G1, U10.2
CLK_U6_1: U6.1, U11.3
GND: C1.2, C2.2, C3.2, C4.2, C5.2, C6.2, C7.2, C8.2, C9.2, C10.2, C11.2, C12.2, C13.2, C14.2, C15.2, C16.2, C17.2, C18.2, C19.2, C23.2, C24.2, C25.2, C26.2, C27.2, C28.2, C29.2, C30.2, C31.2, C32.2, C33.2, C34.2, C35.2, C36.2, C37.2, C38.2, C39.2, C40.2, C41.2, C42.2, C43.2, J1.2, R2.2, R14.2, R16.2, R21.2, R22.2, R23.2, R24.2, R28.2, R31.2, R33.2, U1.D3, U1.F2, U1.F11, U1.F12, U1.J1, U1.K1, U2.7, U2.8, U2.23, U2.24, U2.25, U2.26, U2.27, U2.28, U2.29, U2.30, U2.31, U4.4, U5.1, U5.13, U5.19, U5.20, U5.31, U5.33, U6.4, U6.15, U6.19, U6.25, U6.26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
NET_U1_A3: R10.1, U1.A3, U2.15
NET_U1_A4: R14.1, U1.A4
NET_U1_B4: R12.1, U1.B4, U2.16
NET_U1_C11: C12.1, U1.C11
NET_U1_E3: R16.1, U1.E3
NET_U1_H2: R9.1, U1.H2, U18.4
NET_U1_H3: R15.1, U1.H3
NET_U1_L11: C11.1, U1.L11
NET_U1_M1: C9.1, C10.1, F1.1, U1.L1, U1.M1
NET_U1_M12: U14.3, U14.4
NET_U2_2: R17.2, U2.2
NET_U2_17: R17.1, U2.17
NET_U2_22: R7.1, U2.22, U16.4
NET_U3_1: U2.11, U3.1
NET_U3_2: U2.10, U3.2, U3.3, U3.4
NET_U4_3: R18.1, U4.3
NET_U4_7: R20.1, U4.7
NET_U5_7: R8.1, U5.7, U17.4
NET_U5_21: R21.1, U5.21
NET_U6_20: C28.1, C33.1, U6.20
NET_U7_2: C21.1, R23.1, U7.2
NET_U7_5: C20.1, R22.1, U7.5
NET_U8_5: C22.1, C23.1, R24.1, R25.1, U8.5
NET_U12_1: C35.1, U12.1
NET_U12_6: R27.2, R28.1, U12.6
NET_U12_8: R26.1, U12.8
NET_U13_1: R30.1, R31.1, U13.1
NET_U13_3: R32.2, R33.1, U13.3
NET_U13_4: R29.1, U13.4, U16.2, U17.2, U18.2
NET_U14_1: R2.1, U14.1, U14.2
PROC_I2S2_CK: U1.B8, U6.7
PROC_I2S2_EXT_SD: U1.J3, U6.10
PROC_I2S2_SD: U1.K2, U6.8
PROC_I2S2_WS: U1.B3, U6.9, U6.11
PROC_SPI1_MISO: U1.A7, U4.2
PROC_SPI1_MOSI: U1.C5, U4.5
PROC_SPI1_NSS: R19.1, U1.A9, U4.1
PROC_SPI1_SCK: U1.A8, U4.6
PROC_USART1_CTS: U1.B12, U5.8
PROC_USART1_RTS: U1.A12, U5.6
PROC_USART1_RX: U1.C12, U5.17
PROC_USART1_TX: U1.B5, U5.18
VCC_S1_6V5: C36.1, C39.1, C40.1, J1.1, R26.2, U12.4
VCC_TIER1_3V3: C1.1, C2.1, C3.1, C4.1, C5.1, C6.1, C7.1, C8.1, C17.1, C18.1, C19.1, C24.1, C25.1, C26.1, C27.1, C29.1, C30.1, C31.1, C32.1, C34.1, C37.1, C38.1, C41.1, C42.1, C43.1, F1.2, R7.2, R8.2, R9.2, R10.2, R12.2, R15.2, R18.2, R19.2, R20.2, R27.1, R29.2, R30.2, R32.1, U1.C4, U1.E2, U1.G2, U1.G11, U1.G12, U2.20, U4.8, U5.32, U6.3, U6.5, U6.12, U6.18, U11.4, U12.5, U13.6, U16.5, U17.5, U18.5
